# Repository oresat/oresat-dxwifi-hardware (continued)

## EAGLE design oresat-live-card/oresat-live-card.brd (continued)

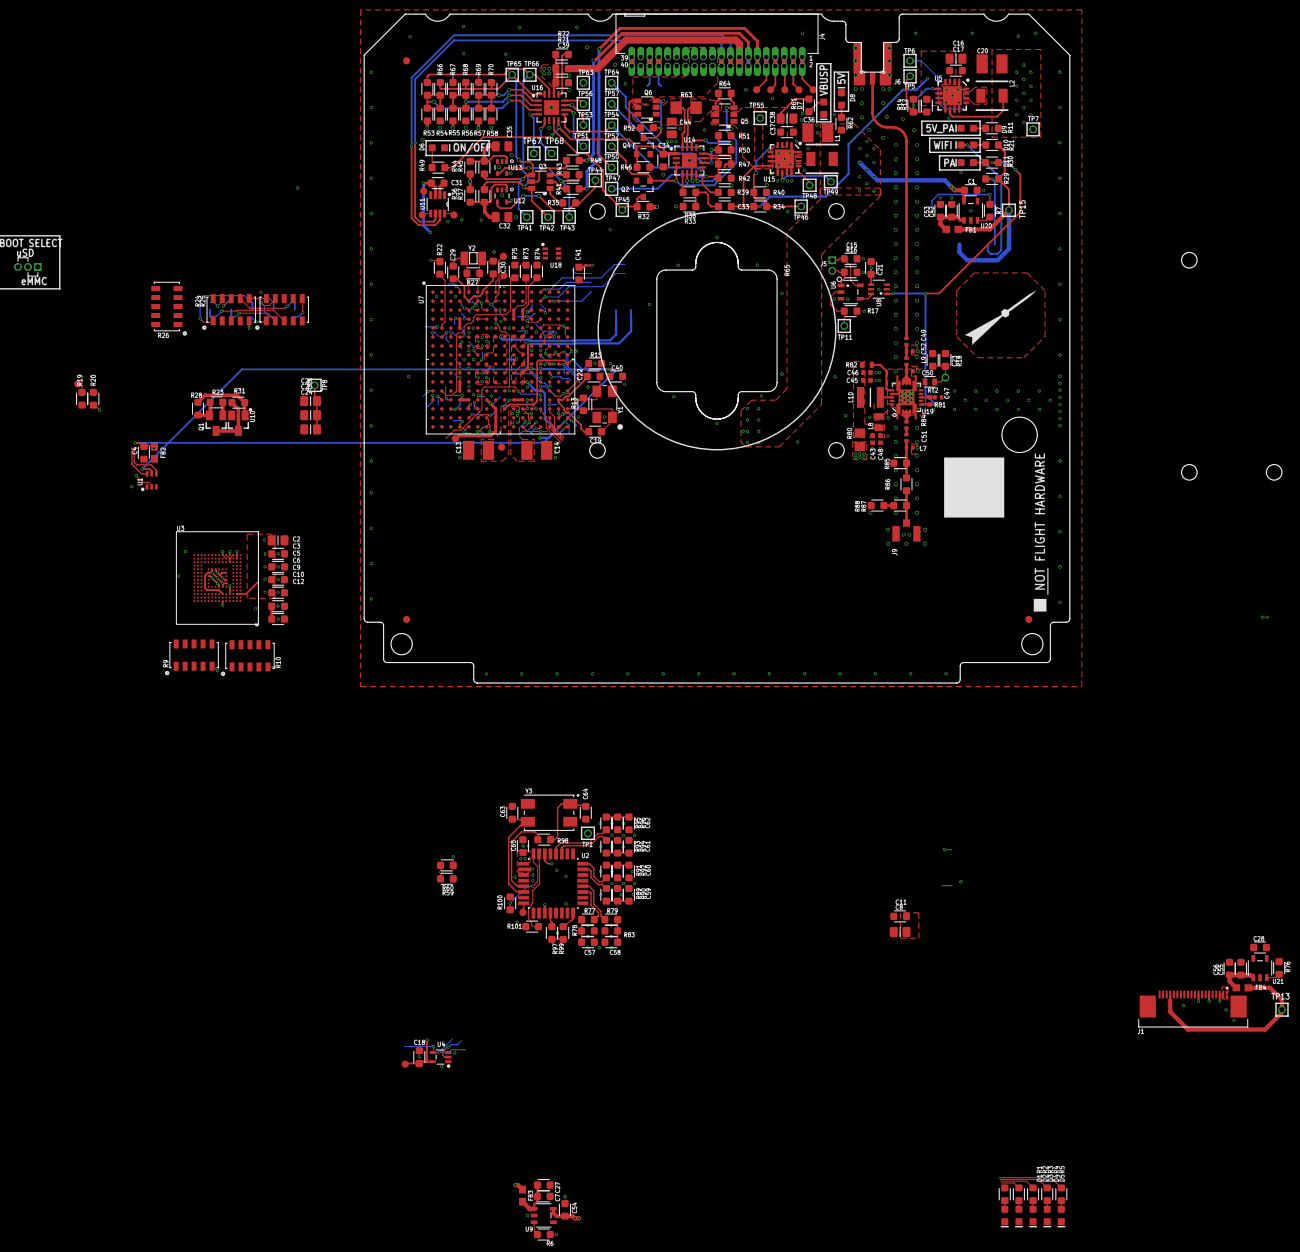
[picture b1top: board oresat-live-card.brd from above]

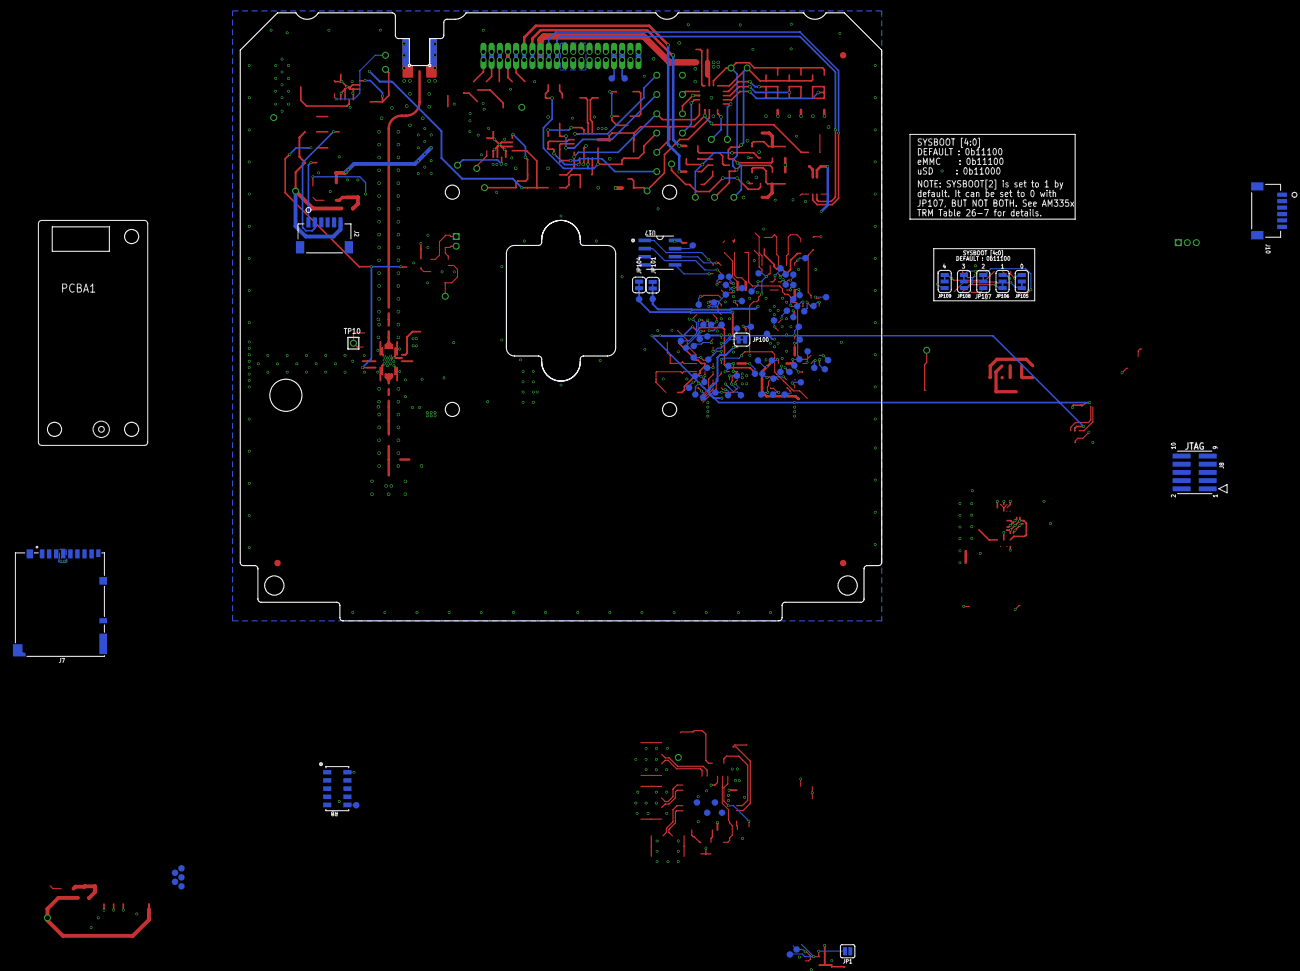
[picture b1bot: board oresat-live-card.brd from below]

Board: 4 copper layers, 99.8 x 94.6 mm, 376 parts (102 on the bottom side), 292 nets.

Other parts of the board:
U$2, U$5, U$6: FIDUCIAL_G10
U$3: PSAS_LOGO_10X10
U$4: FLIGHTMARKER_NEW_BOARDS

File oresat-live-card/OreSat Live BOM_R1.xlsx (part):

Part | Qty per board | Extended Qty | Extras | Qty Needed | Qty on Hand | Qty to Order | Value | Package | MFR | MPN | Alt MFR | Alt MPN | DESCRIPTION
C1, C2, C7, C8, C16, C38, C44 | 7 | 28 | 2 | 30 | 9 | 20 | 10uF | .0805-B | TDK Corporation | CGA4J1X7S1C106M125AE |  | CGA4J1X7S1C106K125AE | CAP CER 10UF 16V X7S 0805
C13, C14, C20, C36 | 4 | 16 | 4 | 20 | 15 | 5 | 22uF | C1210 | TDK Corporation | CGA6P1X7R1C226M250AC |  |  | CAP CER 22UF 16V X7R 1210
C19, C22, C29, C30 | 4 | 16 | 4 | 20 | 8 | 10 | 12pF | .0603-A | TDK Corporation | CGA3E2C0G1H120J080AA |  |  | CAP CER 12PF 50V C0G 0603
C24, C25 | 2 | 8 | 2 | 10 | 4 | 10 | 1000PF | .0805-B | TDK Corporation | CGA4F2X7R2A102K085AE |  |  | CAP CER 1000PF 100V X7R 0805
C26 | 1 | 4 | 6 | 10 | 7 | 0 | 0.1uF | .0805-B | TDK Corporation | CGA4J2X7R1H104K125AE |  |  | CAP CER 0.1UF 50V X7R 0805
C3, C5, C6, C9, C10, C12, C17, C33, C34, C37 | 10 | 40 | 10 | 50 | 20 | 30 | 1uF | .0603-A | TDK Corporation | CGA3E1X7R1C105K080AC |  |  | CAP CER 1UF 16V X7R 0603
C32, C35 | 2 | 8 | 2 | 10 | 4 | 10 | 1uF | .0805-B-NOSILK | TDK Corporation | CGA4J2X7R1C105K125AA |  |  | CAP CER 1UF 16V X7R 0805
C4, C11, C15, C18, C21, C23, C31, C39, C40, C41 | 10 | 40 | 10 | 50 | 17 | 30 | 0.1uF | .0603-A | TDK Corporation | CGA3E2X7R1E104K080AA |  |  | CAP CER 0.1UF 25V X7R 0603
C43, C45, C46, C47 | 4 | 16 | 4 | 20 | 8 | 10 | 0.1uF | .0402-B-NOSILK | TDK Corporation | CGA2B1X7R1C104K050BC |  |  | CAP CER 0.1UF 16V X7R 0402
C48 | 1 | 4 | 6 | 10 | 14 | 0 | 1000pF | .0402-B-NOSILK | TDK Corporation | CGA2B2NP01H102J050BA |  |  | CAP CER 1000PF 50V NP0 0402
C49 | 1 | 4 | 6 | 10 | 25 | 0 | 100pF | .0402-C-NOSILK | Murata | GCM1555C1H101GA16D |  |  | CAP CER 100PF 50V C0G/NP0 0402
C50 | 1 | 4 | 6 | 10 | 3 | 10 | 3.0pF | .0402-C-NOSILK | AVX | 04025U3R0BAT2A |  |  | CAP CER 3PF 50V NP0 0402
C51 | 1 | 4 | 6 | 10 | 1 | 10 | 1.1pF | .0402-C-NOSILK | AVX | 04025J1R1PBSTR\500 |  |  | 50V 1.1pF .02pFTol ThinFilm 0402
C51a | 1 | 4 | 6 | 10 | 1 | 10 | 1.4pF | .0402-C-NOSILK | AVX | 04025J1R4PBSTR\500 |  |  | 50V 1.4pF .02pFTol ThinFilm 0402
C52 | 1 | 4 | 6 | 10 | 3 | 10 | 1.6pF | .0402-C-NOSILK | AVX | 04025U1R6BAT2A |  |  | CAP CER 1.6PF 50V NP0 0402
D1, D7, D8 | 3 | 12 | 3 | 15 | 5 | 10 | GREEN | LED-0603 | Würth Elektronik | 150060GS75020 |  |  | Green 525nm LED 3.2V 0603
D2, D3, D4, D5 | 4 | 16 | 4 | 20 | 8 | 10 | BLUE | LED-0603 | Würth Elektronik | 150060BS75020 |  |  | Blue 470nm LED 3.2V 0603
D6 | 1 | 4 | 6 | 10 | 10 | 0 | GREEN | LED-0603 | Würth Elektronik | 150060VS55040 |  |  | Green 573nm LED 2V 0603
D9, D10 | 2 | 8 | 2 | 10 | 1 | 10 | GREEN | LED-0603 | Lite-On Inc. | LTST-C193KGKT-5A |  |  | Green 572nm LED 2V 0603
D11 | 1 | 4 | 6 | 10 | 8 | 0 | RED | LED-0603 | Lite-On Inc. | LTST-C193KRKT-5A |  |  | Red 631nm LED 2V 0603
FB1, FB2 | 2 | 8 | 2 | 10 | 4 | 10 | 30Ω/1.8A | 0603 | Murata Electronics | BLM18KG300JH1D |  |  | FERRITE BEAD 30 OHM 0603 1 LN
J1 | 1 | 4 | 1 | 5 | 3 | 2 | ORESAT-DEBUG-CONNECTOR-CARD | TE_2-1734592-0 | TE Connectivity AMP Connectors | 2-1734592-0 |  |  | CONN FPC BOTTOM 20POS 0.50MM R/A
J2 | 1 | 4 | 1 | 5 | 3 | 2 | SM06B-SRSS-TB(LF)(SN) | CONN_SM06B-SRSS-TB_JST | JST Sales America Inc. | SM06B-SRSS-TB(LF)(SN) |  |  | CONN HEADER SMD R/A 6POS 1MM
J4 | 1 | 4 | 1 | 5 | 0 | 5 | TFM-120-01-L-D-RA | J-SAMTEC-TFM-120-X1-XXX-D-RA | Samtec Inc. | TFM-120-01-L-D-RA |  |  | CONN HEADER R/A 40POS 1.27MM
J6 | 1 | 4 | 1 | 5 | 5 | 0 | J-MOLEX-SMPM-73300-003X | J-MOLEX-SMPM-073300-003X | MOLEX | 0733000020 |  |  | CONN SMPM PLUG STR EDGEMNT
J7 | 1 | 4 | 1 | 5 | 2 | 3 | DM3BT-DSF-PEJS | DM3BT-DSF-PEJS | Hirose Electric Co Ltd | DM3BT-DSF-PEJS |  |  | CONN MICRO SD CARD PUSH-PUSH R/A
J9 | 1 | 4 | 1 | 5 | 3 | 2 | U.FL-R-SMA | U.FL-R-SMT | Hirose Electric Co Ltd | U.FL-R-SMT-1(10) |  |  | CONN U.FL RCPT STR 50 OHM SMD
L1,L2 | 2 | 8 | 2 | 10 | 4 | 6 | 6.8uH | ECS-MPI4040 | ECS Inc. | ECS-MPI4040R4-6R8-R |  |  | FIXED IND 6.8UH 2.4A 91 MOHM SMD
L7 | 1 | 4 | 6 | 10 | 5 | 0 | 1.7nH | .0402-C-NOSILK | Coilcraft | 0402DC-1N7XJRU |  |  | 1.7nH RF Inductor, ceramic core, 5% tol
L8 | 1 | 4 | 6 | 10 | 4 | 0 | 6.8nH | .0805-C-NOSILK | Coilcraft | 0805CS-060XJLC |  |  | Fixed Inductors 0805CS 6.8 nH 5 % 0.6 A
L9 | 1 | 4 | 6 | 10 | 13 | 0 | 1.0nH | .0402-C-NOSILK | TDK Corporation | MLK1005S1N0ST000 |  |  | FIXED IND 1NH 500MA 100 MOHM SMD
L10 | 1 | 4 | 6 | 10 | 3 | 2 | 10nH | INDC2928X203N | Coilcraft | 1008HQ-10NXJLB |  |  | Fixed Inductors 1008 10nH Unshld 5%
Q1 | 1 | 4 | 2 | 6 | 3 | 2 | MMBT2907 | SOT23-BEC | Diodes Incorporated | MMBT2907A-7-F |  |  | TRANS PNP 60V 0.6A SOT23-3
Q2, Q4 | 2 | 8 | 2 | 10 | 4 | 6 | PMV45EN | SOT23 | Nexperia USA Inc. | PMV45EN2R |  |  | MOSFET N-CH 30V 4.1A TO236AB
Q3 | 1 | 4 | 2 | 6 | 3 | 2 | DMP2240UDM | SOT23-6 | Diodes Incorporated | DMP2240UDM-7 |  |  | MOSFET 2P-CH 20V 2A SOT-26
Q5, Q6 | 2 | 8 | 2 | 10 | 4 | 6 | MOSFET-PCH-SOT23-6 | SOT23-6 | Diodes Incorporated | DMP3050LVT-7 |  |  | MOSFET P CH 30V 4.5A TSOT26
R1, R2, R3, R4, R5, R21, R30 | 7 | 28 | 4 | 32 | 11 | 20 | 1k | .0603-A | Panasonic Electronic Components | ERJ-3EKF1001V |  | ERJ-U03F1001V | RES SMD 1K OHM 1% 1/10W 0603
R11, R49, R61, R62 | 4 | 16 | 4 | 20 | 8 | 10 | 2.7k | .0603-A | Panasonic Electronic Components | ERJ-3EKF2701V |  | ERJ-U03F2701V | RES SMD 2.7K OHM 1% 1/10W 0603
R13, R36, R44 | 3 | 12 | 3 | 15 | 6 | 10 | 1M | .0603-A | Panasonic Electronic Components | ERJ-3EKF1004V |  | ERJ-U03F1004V | RES SMD 1M OHM 1% 1/10W 0603
R23 | 1 | 4 | 6 | 10 | 6 | 10 | 499 | .0603-A | Panasonic Electronic Components | ERJ-3EKF4990V |  |  | RES SMD 499 OHM 1% 1/10W 0603
R24, R25, R26 | 3 | 12 | 3 | 15 | 6 | 10 | 100K | ARRAY_EXBA-M | Panasonic Electronic Components | EXB-A10P104J |  |  | RES ARRAY 8 RES 100K OHM 2512
R29, R47, R50 | 3 | 12 | 3 | 15 | 13 | 0 | 0 | .0603-A | Panasonic Electronic Components | ERJ-3GEY0R00V |  |  | RES SMD 0 OHM JUMPER 1/10W 0603
R31 | 1 | 4 | 6 | 10 | 7 | 10 | 40.2K | .0603-A | Panasonic Electronic Components | ERJ-3EKF4022V |  |  | RES SMD 40.2K OHM 1% 1/10W 0603
R33 | 1 | 4 | 6 | 10 | 7 | 10 | 100k | .0603-A | Panasonic Electronic Components | ERJ-PA3F1003V |  |  | RES SMD 100K OHM 1% 1/4W 0603
R35, R43 | 2 | 8 | 2 | 10 | 4 | 10 | 665k | .0603-A | Panasonic Electronic Components | ERJ-3EKF6653V |  |  | RES SMD 665K OHM 1% 1/10W 0603
R37, R45 | 2 | 8 | 2 | 10 | 4 | 10 | 330k | .0603-A | Panasonic Electronic Components | ERJ-3EKF3303V |  |  | RES SMD 330K OHM 1% 1/10W 0603
R41, R48, R71, R73, R74, R75 | 6 | 24 | 4 | 28 | 10 | 20 | 100 | .0603-A | Panasonic Electronic Components | ERJ-3EKF1000V |  |  | RES SMD 100 OHM 1% 1/10W 0603
R6, R7, R12, R15, R16, R17, R18, R19, R20, R22, R28, R32, R34, R38, R39, R46, R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 | 19 | 76 | 24 | 100 | 43 | 50 | 10k | .0603-A | Panasonic Electronic Components | ERJ-3EKF1002V |  | ERJ-U03F1002V | RES SMD 10K OHM 1% 1/10W 0603
R63 | 1 | 4 | 2 | 6 | 3 | 2 | 100m | R1206 | Vishay Dale | RCWE1206R100FKEA |  |  | RES 0.1 OHM 1% 1/2W 1206
R8, R9, R10 | 3 | 12 | 3 | 15 | 9 | 6 | 10K | ARRAY_EXBA-M | Panasonic Electronic Components | EXB-A10P103J |  |  | RES ARRAY 8 RES 10K OHM 2512
R80 | 1 | 4 | 6 | 10 | 14 | 0 | 0 | R0805 | Panasonic Electronic Components | ERJ-6GEY0R00V |  |  | RES SMD 0 OHM JUMPER 1/8W 0805
R81 | 1 | 4 | 6 | 10 | 13 | 0 | 110 | .0402-B-NOSILK | Panasonic Electronic Components | ERJ-2RKF1100X |  | ERJ-U02F1100X | RES SMD 110 OHM 1% 1/10W 0402
R82 | 1 | 4 | 6 | 10 | 14 | 0 | 220 | .0603-C-NOSILK | Panasonic Electronic Components | ERJ-3EKF2200V |  | ERJ-U03F2200V | RES SMD 220 OHM 1% 1/10W 0603
R84 | 1 | 4 | 6 | 10 | 17 | 0 | 3.3 | .0402-C-NOSILK | Vishay / Dale | CRCW04023R30FKED |  |  | RES SMD 3.3 OHM 1% 1/16W 0402
R85 | 1 | 4 | 6 | 10 | 7 | 0 | 82.5 | .0603-A | Panasonic Electronic Components | ERJ-3EKF82R5V |  |  | RES SMD 82.5 OHM 1% 1/10W 0603
R86 | 1 | 4 | 6 | 10 | 7 | 0 | 93.1 | .0603-A | Panasonic Electronic Components | ERJ-3EKF93R1V |  |  | RES SMD 93.1 OHM 1% 1/10W 0603
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
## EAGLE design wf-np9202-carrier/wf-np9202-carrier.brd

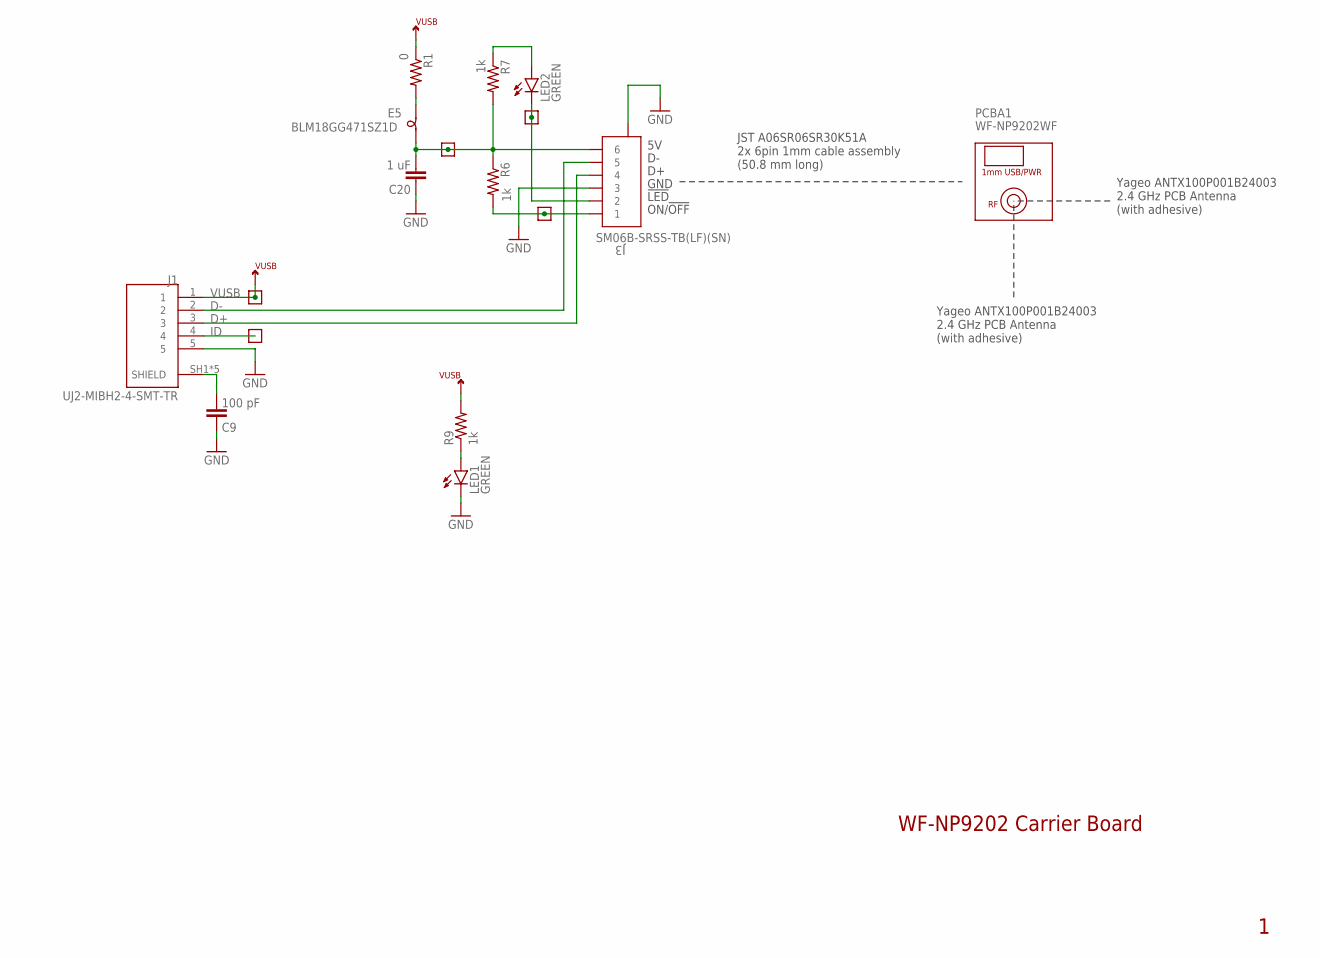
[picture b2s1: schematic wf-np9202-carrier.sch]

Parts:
C9: 100 pF; .0603-C-NOSILK
C20: 1 uF; .0603-B-NOSILK
E5: BLM18GG471SZ1D; .0603-B
ID: TEST-POINT-LARGE-SQUARE; 1X01
J1: UJ2-MIBH2-4-SMT-TR; CUI_UJ2-MIBH2-4-SMT-TR
J3: SM06B-SRSS-TB(LF)(SN); CONN_SM06B-SRSS-TB_JST
LED1, LED2: GREEN; LED-0603
PCBA1: WF-NP9202WF; WF-NP9202
R1: 0; .0603-B-NOSILK
R6, R7, R9: 1k; .0603-B-NOSILK
TP1, TP3, TP4, TP5: TEST-POINT-LARGE-SQUARE; 1X01

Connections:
D+: J1.3, J3.4
D-: J1.2, J3.5
GND: C9.1, C20.1, J1.5, J3.3, J3.7, J3.8 (7), LED1.C
ID: ID.1, J1.4
unnamed: C9.2, J1.SH1 (SHIELD), J1.SH2 (SHIELD), J1.SH3 (SHIELD), J1.SH4 (SHIELD), J1.SH5 (SHIELD)
unnamed: LED1.A, R9.1
unnamed: C20.2, E5.2, J3.6, R6.1, R7.2, TP3.1
unnamed: E5.1, R1.2
unnamed: J3.1, R6.2, TP4.1
unnamed: LED2.A, R7.1
unnamed: J3.2, LED2.C, TP5.1
VUSB: J1.1, R1.1, R9.2, TP1.1

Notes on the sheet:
WF-NP9202 Carrier Board
GND
!LED
ON/!OFF
JST A06SR06SR30K51A 2x 6pin 1mm cable assembly (50.8 mm long)
Yageo ANTX100P001B24003 2.4 GHz PCB Antenna (with adhesive)

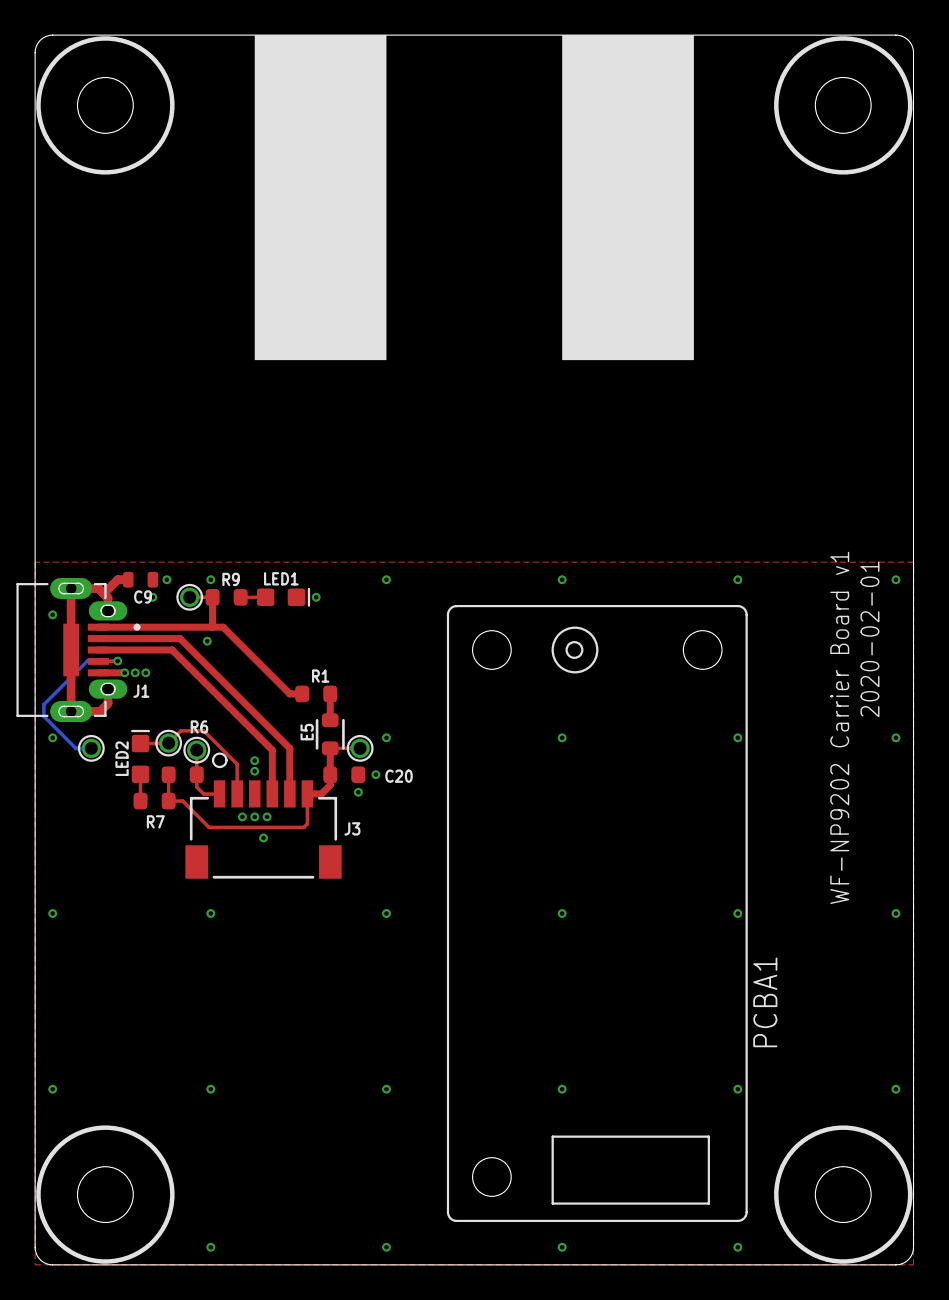
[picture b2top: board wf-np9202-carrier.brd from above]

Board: 2 copper layers, 50.0 x 70.0 mm, 21 parts (0 on the bottom side), 12 nets.

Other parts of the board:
U$1, U$2, U$3, U$4: #4/.300-BARE+STD_NUT_OR_STAR_WASHER

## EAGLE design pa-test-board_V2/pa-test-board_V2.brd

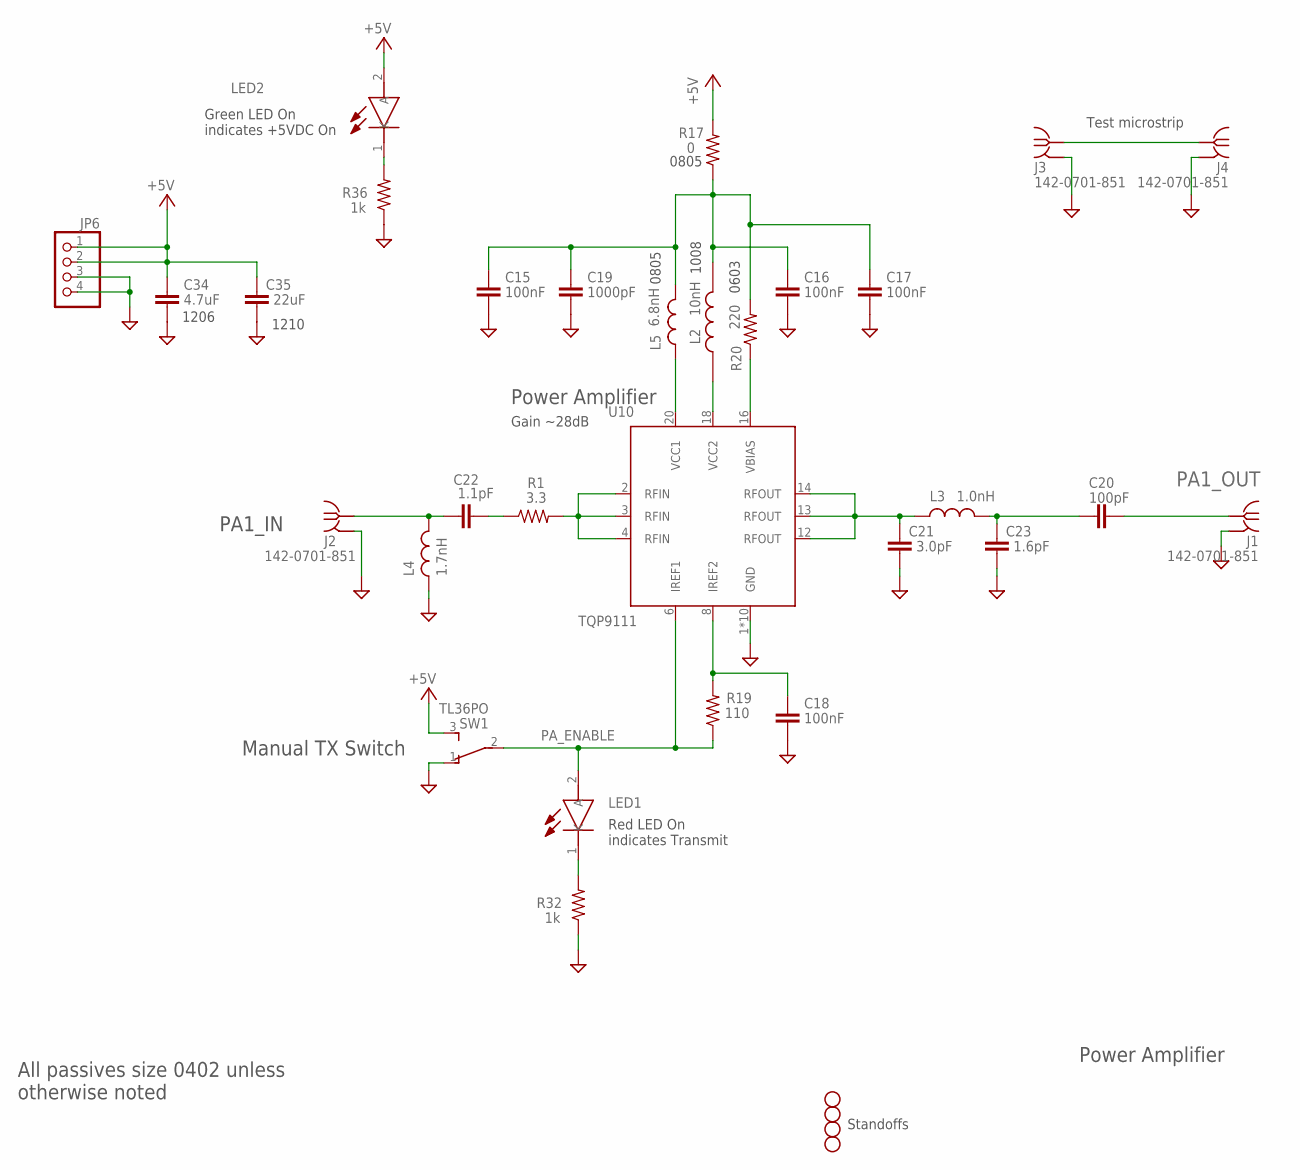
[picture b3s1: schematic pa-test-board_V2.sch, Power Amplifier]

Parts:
C15, C16, C17: 100nF; .0402-B-NOSILK; MPN CGA2B1X7R1C104K050BC
C18: 100nF; .0402-C-NOSILK; MPN CGA2B1X7R1C104K050BC
C19: 1000pF; .0402-B-NOSILK; MPN CGA2B2NP01H102J050BA
C20: 100pF; .0402-C-NOSILK; MPN GCM1885C1H101JA16D
C21: 3.0pF; .0402-C-NOSILK; MPN 04025U3R0BAT2A
C22: 1.1pF; .0402-C-NOSILK; MPN 04025J1R1PBSTR\500
C23: 1.6pF; .0402-C-NOSILK; MPN 04025U1R6BAT2A
C34: 4.7uF; C1206; MPN GCJ31CR71C475KA01L
C35: 22uF; C1210; MPN GCJ32ER71C226KE01L
H1, H2, H3, H4: STAND-OFFTIGHT; STAND-OFF-TIGHT
J1, J2, J3, J4: 142-0701-851; MPN 142-0701-851
JP6: PINHD-1X4; 1X04; MPN 0022232041
L2: 10nH; INDC2928X203N
L3: 1.0nH; .0402-C-NOSILK; MPN MLK1005S1N0ST000
L4: 1.7nH; .0402-C-NOSILK; MPN 0402DC-1N7XJRU
L5: 6.8nH; .0805-C-NOSILK; MPN 0805CS-060XJLC
LED1: LTST-C193KRKT-5A; LEDC1607X80N
LED2: LTST-C193KGKT-5A; LEDC1607X80N
R1: 3.3; .0402-C-NOSILK; MPN CRCW04023R30FKED
R17: 0; R0805; MPN ERJ-6GEY0R00V
R19: 110; .0402-B-NOSILK; MPN ERJ-2RKF1100X
R20: 220; .0603-C-NOSILK; MPN ERJ-3EKF2200V
R32, R36: 1k; .0402-B-NOSILK; MPN ERJ-2GEJ102X
SW1: TL36PO; TL3XPO; MPN TL36P005000
U10: TQP9111; QFN50P400X400X102-21N

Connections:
+5V: C34.1, C35.1, JP6.1, JP6.2, LED2.2 (A), R17.2, SW1.3 (S)
GND: C15.2, C16.2, C17.2, C18.2, C19.2, C21.2, C23.2, C34.2, C35.2, J1.GND1 (GND), J1.GND2 (GND), J1.GND3 (GND), J1.GND4 (GND), J2.GND1 (GND), J2.GND2 (GND), J2.GND3 (GND), J2.GND4 (GND), J3.GND1 (GND), J3.GND2 (GND), J3.GND3 (GND), J3.GND4 (GND), J4.GND1 (GND), J4.GND2 (GND), J4.GND3 (GND), J4.GND4 (GND), JP6.3, JP6.4, L4.1, R32.1, R36.1, SW1.1 (O), U10.1 (GND), U10.5 (GND), U10.7 (GND), U10.9 (GND), U10.10 (GND), U10.11 (GND), U10.15 (GND), U10.17 (GND), U10.19 (GND), U10.21 (GND)
unnamed: C22.1, J2.RF1 (RF), L4.2
unnamed: J3.RF1 (RF), J4.RF1 (RF)
unnamed: L2.1, U10.18 (VCC2)
unnamed: C22.2, R1.1
unnamed: LED1.1 (K), R32.2
unnamed: C15.1, C16.1, C17.1, C19.1, L2.2, L5.2, R17.1, R20.2
unnamed: C18.1, R19.2, U10.8 (IREF2)
unnamed: C21.1, L3.1, U10.12 (RFOUT), U10.13 (RFOUT), U10.14 (RFOUT)
unnamed: C20.1, C23.1, L3.2
unnamed: R20.1, U10.16 (VBIAS)
unnamed: L5.1, U10.20 (VCC1)
unnamed: LED2.1 (K), R36.2
unnamed: R1.2, U10.2 (RFIN), U10.3 (RFIN), U10.4 (RFIN)
PA1_OUT: C20.2, J1.RF1 (RF)
PA_ENABLE: LED1.2 (A), R19.1, SW1.2, U10.6 (IREF1)

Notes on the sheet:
0805
0603
Power Amplifier
Gain ~28dB
PA1_IN
All passives size 0402 unless otherwise noted
1206
1210
Manual TX Switch
Red LED On indicates Transmit
Green LED On indicates +5VDC On
Standoffs
Test microstrip
1008

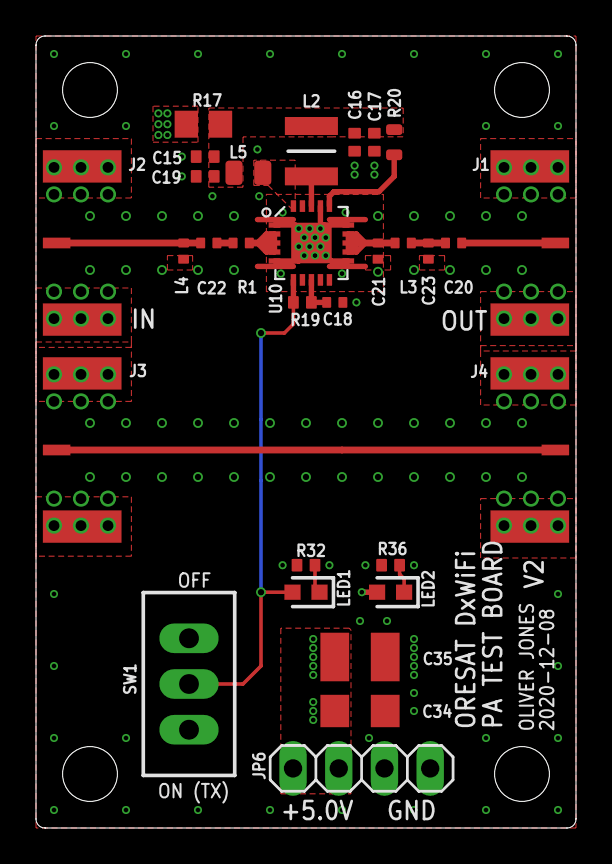
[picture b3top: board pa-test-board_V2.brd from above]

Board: 4 copper layers, 30.0 x 44.0 mm, 34 parts (0 on the bottom side), 17 nets.

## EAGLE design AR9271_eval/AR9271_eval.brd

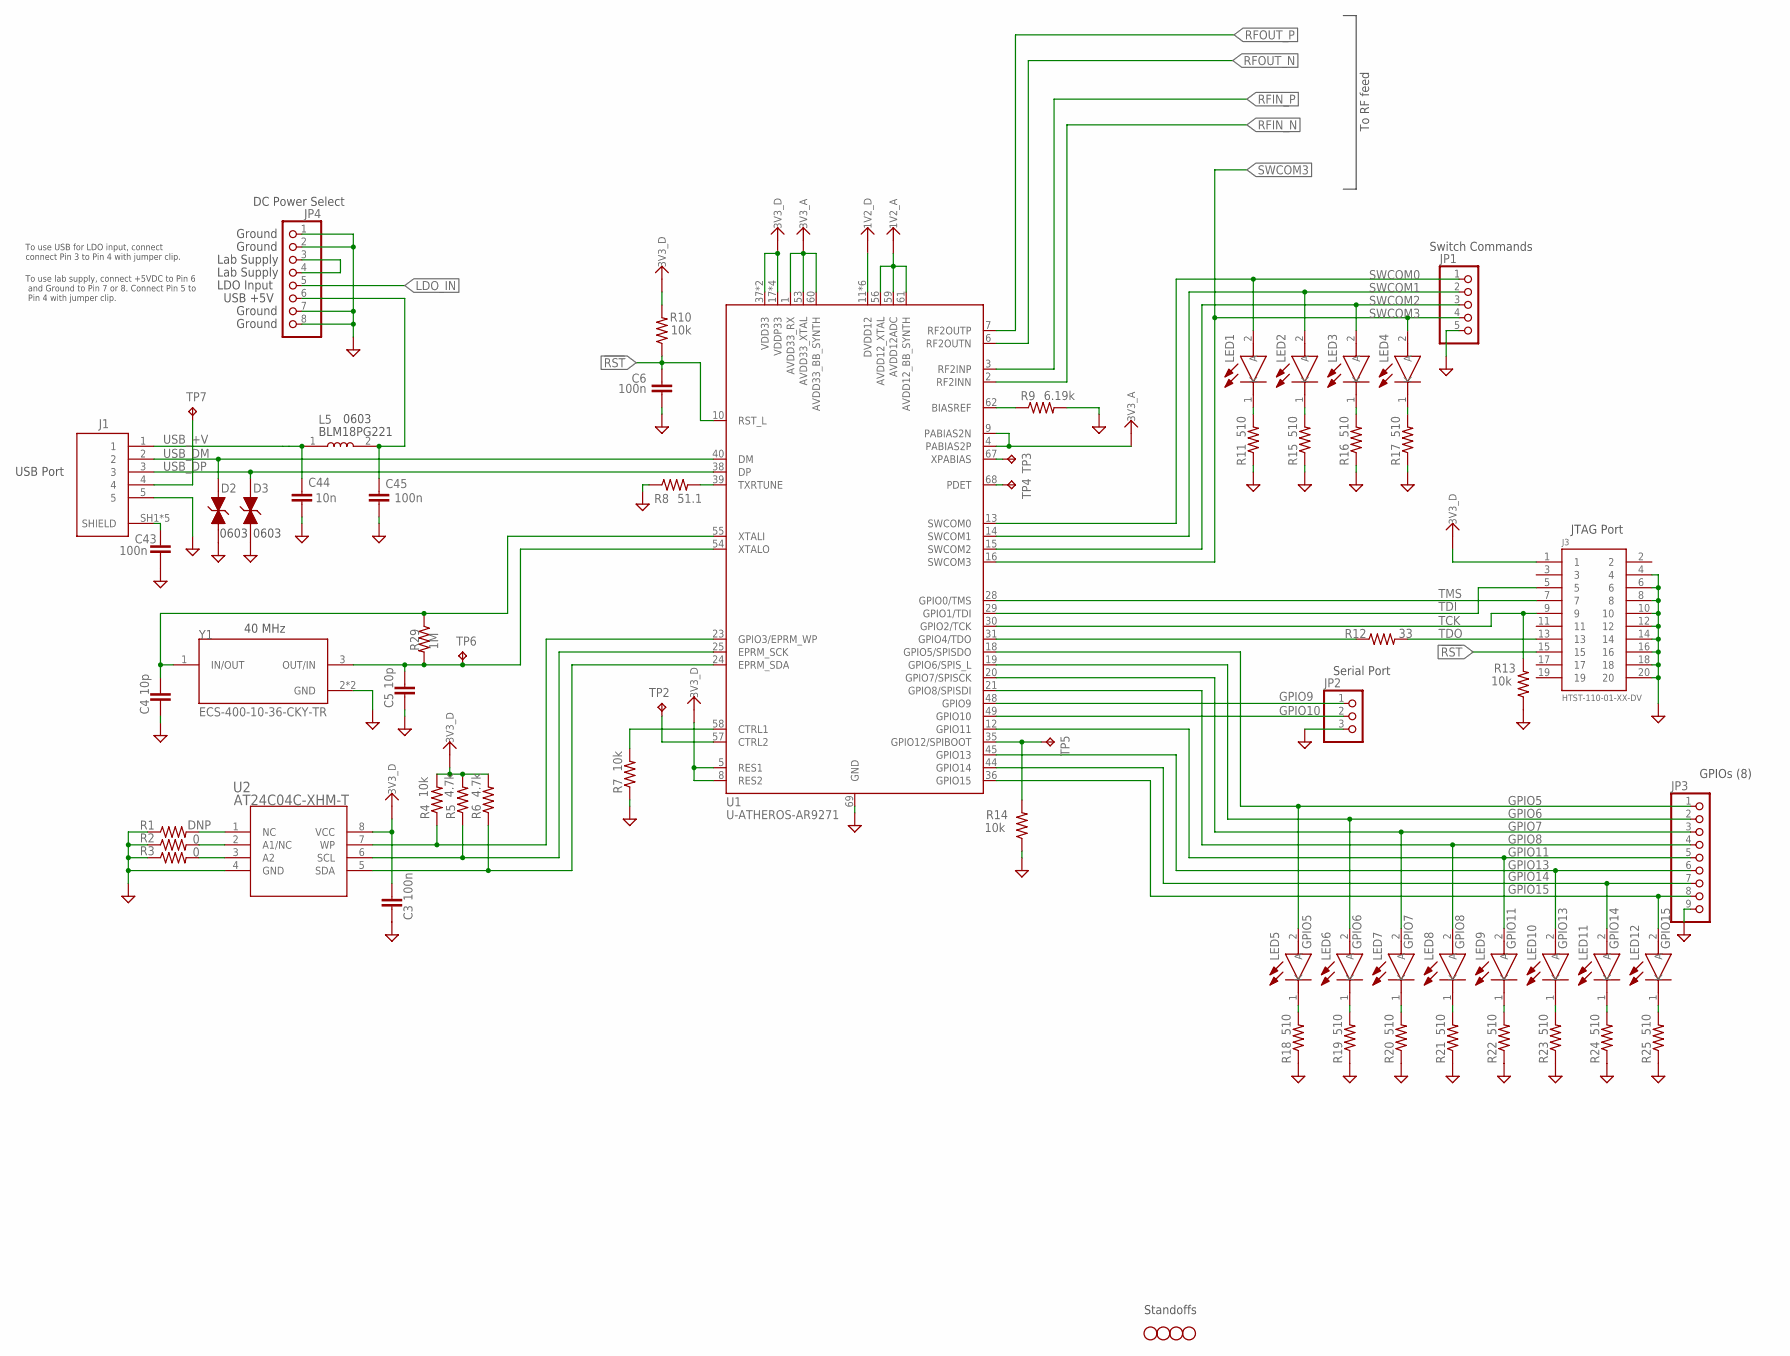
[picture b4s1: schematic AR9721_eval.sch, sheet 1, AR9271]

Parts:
C3, C6, C43, C45: 100n; .0402-B-NOSILK; MPN CGA2B1X7R1C104K050BC
C4, C5: 10p; .0402-B-NOSILK
C44: 10n; .0402-B-NOSILK; MPN C0402C103K4RACAUTO
D2, D3: PGB1010603MR; ESD_PGB1010603MR; MPN PGB1010603MR
H1, H2, H3, H4: STAND-OFFTIGHT; STAND-OFF-TIGHT
J1: UJ2-MIBH2-4-SMT-TR; CUI_UJ2-MIBH2-4-SMT-TR; MPN UJ2-MIBH2-4-SMT-TR
J3: HTST-110-01-XX-DV; MPN HTST-110-01-L-DV-P
JP1: PINHD-1X5; 1X05
JP2: PINHD-1X3; 1X03
JP3: PINHD-1X9; 1X09
JP4: PINHD-1X8; 1X08
L5: BLM18PG221SH1D; INDC1608X95; MPN BLM18PG221SH1D
LED1, LED2, LED3, LED4, LED5, LED6, LED7, LED8, LED9, LED10, LED11, LED12: LTST-C193KGKT-5A; LEDC1607X80N
R1: DNP; .0402-A-NOSILK; MPN ERJ-2GE0R00X
R2, R3: 0; .0402-A-NOSILK; MPN ERJ-2GE0R00X
R4, R7, R10, R13, R14: 10k; .0402-A-NOSILK; MPN ERJ-2GEJ103X
R5, R6: 4.7k; .0402-A-NOSILK; MPN ERJ-2GEJ103X
R8: 51.1; .0402-A-NOSILK; MPN ERJ-2RKF51R1X
R9: 6.19k; .0402-A-NOSILK; MPN ERJ-2RKF6191X
R11, R15, R16, R17, R18, R19, R20, R21, R22, R23, R24, R25: 510; .0402-A-NOSILK; MPN ERJ-2GEJ511X
R12: 33; .0402-A-NOSILK; MPN ERJ-2GEJ330X
R29: 1M; .0402-A-NOSILK; MPN ERJ-2GEJ105X
TP2, TP3, TP4, TP5, TP6, TP7: TPTP06R; TP06R
U1: U-ATHEROS-AR9271; QFN-68; MPN AR9271
U2: AT24C04C-XHM-T; 8X
Y1: ECS-400-10-36-CKY-TR; XTAL_ECS-400-10-36-CKY-TR

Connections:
1V2_A: U1.56 (AVDD12_XTAL), U1.59 (AVDD12ADC), U1.61 (AVDD12_BB_SYNTH); also elsewhere on the board
1V2_D: U1.11 (DVDD12), U1.22 (DVDD12), U1.27 (DVDD12), U1.42 (DVDD12), U1.43 (DVDD12), U1.46 (DVDD12); also elsewhere on the board
3V3_A: U1.1 (AVDD33_RX), U1.4 (PABIAS2P), U1.9 (PABIAS2N), U1.53 (AVDD33_XTAL), U1.60 (AVDD33_BB_SYNTH); also elsewhere on the board
3V3_D: C3.1, J3.1, R4.2, R5.2, R6.2, R10.2, U1.5 (RES1), U1.8 (RES2), U1.17 (VDDP33), U1.26 (VDDP33), U1.33 (VDDP33), U1.37 (VDD33), U1.41 (VDD33), U1.47 (VDDP33), U2.8 (VCC); also elsewhere on the board
!RST: C6.1, J3.15, R10.1, U1.10 (RST_L)
A1: R2.2, U2.2 (A1/NC)
A2: R3.2, U2.3 (A2)
BIASREF: R9.1, U1.62 (BIASREF)
CTRL1: R7.2, U1.58 (CTRL1)
CTRL2: TP2.TP, U1.57 (CTRL2)
EE-SCK: R5.1, U1.25 (EPRM_SCK), U2.6 (SCL)
EE-SDA: R6.1, U1.24 (EPRM_SDA), U2.5 (SDA)
EE-WP: R4.1, U1.23 (GPIO3/EPRM_WP), U2.7 (WP)
GND: C3.2, C4.2, C5.2, C6.2, C43.2, C44.2, C45.2, D2.2, D3.2, J1.5, J3.4, J3.6, J3.8, J3.10, J3.12, J3.14, J3.16, J3.18, J3.20, JP1.5, JP2.3, JP3.9, JP4.1, JP4.2, JP4.7, JP4.8, R1.1, R2.1, R3.1, R7.1, R8.1, R9.2, R11.1, R13.1, R14.1, R15.1, R16.1, R17.1, R18.1, R19.1, R20.1, R21.1, R22.1, R23.1, R24.1, R25.1, U1.69 (GND), U2.4 (GND), Y1.2 (GND), Y1.4 (GND); also elsewhere on the board
GPIO5: JP3.1, LED5.2 (A), U1.18 (GPIO5/SPISDO)
GPIO6: JP3.2, LED6.2 (A), U1.19 (GPIO6/SPIS_L)
GPIO7: JP3.3, LED7.2 (A), U1.20 (GPIO7/SPISCK)
GPIO8: JP3.4, LED8.2 (A), U1.21 (GPIO8/SPISDI)
GPIO9: JP2.1, U1.48 (GPIO9)
GPIO10: JP2.2, U1.49 (GPIO10)
GPIO11: JP3.5, LED9.2 (A), U1.12 (GPIO11)
GPIO13: JP3.6, LED10.2 (A), U1.45 (GPIO13)
GPIO14: JP3.7, LED11.2 (A), U1.44 (GPIO14)
GPIO15: JP3.8, LED12.2 (A), U1.36 (GPIO15)
LDO_IN: JP4.5; also elsewhere on the board
unnamed: J1.4, TP7.TP
unnamed: JP4.3, JP4.4
unnamed: R1.2, U2.1 (NC)
unnamed: LED1.1 (K), R11.2
unnamed: LED2.1 (K), R15.2
unnamed: LED3.1 (K), R16.2
unnamed: LED4.1 (K), R17.2
unnamed: LED5.1 (K), R18.2
unnamed: LED6.1 (K), R19.2
unnamed: LED7.1 (K), R20.2
unnamed: LED8.1 (K), R21.2
unnamed: LED9.1 (K), R22.2
unnamed: C43.1, J1.SH1 (SHIELD), J1.SH2 (SHIELD), J1.SH3 (SHIELD), J1.SH4 (SHIELD), J1.SH5 (SHIELD)
unnamed: LED10.1 (K), R23.2
unnamed: LED11.1 (K), R24.2
unnamed: LED12.1 (K), R25.2
PDET: TP4.TP, U1.68 (PDET)
RFIN_N: U1.2 (RF2INN); also elsewhere on the board
RFIN_P: U1.3 (RF2INP); also elsewhere on the board
RFOUT_N: U1.6 (RF2OUTN); also elsewhere on the board
RFOUT_P: U1.7 (RF2OUTP); also elsewhere on the board
SPIBOOT: R14.2, TP5.TP, U1.35 (GPIO12/SPIBOOT)
SWCOM0: JP1.1, LED1.2 (A), U1.13 (SWCOM0)
SWCOM1: JP1.2, LED2.2 (A), U1.14 (SWCOM1)
SWCOM2: JP1.3, LED3.2 (A), U1.15 (SWCOM2)
SWCOM3: JP1.4, LED4.2 (A), U1.16 (SWCOM3); also elsewhere on the board
TCK: J3.9, R13.2, U1.30 (GPIO2/TCK)
TDI: J3.5, U1.29 (GPIO1/TDI)
TDO: J3.13, R12.2
TDO-PRE-RES: R12.1, U1.31 (GPIO4/TDO)
TMS: J3.7, U1.28 (GPIO0/TMS)
TXRTUNE: R8.2, U1.39 (TXRTUNE)
USB+5V: C45.1, JP4.6, L5.2
USB_+V: C44.1, J1.1, L5.1
USB_DM: D2.1, J1.2, U1.40 (DM)
USB_DP: D3.1, J1.3, U1.38 (DP)
XPABIOS: TP3.TP, U1.67 (XPABIAS)
XTALI: C4.1, R29.1, U1.55 (XTALI), Y1.1 (IN/OUT)
XTALO: C5.1, R29.2, TP6.TP, U1.54 (XTALO), Y1.3 (OUT/IN)

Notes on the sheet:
Lab Supply
LDO Input
USB +5V
Ground
To use USB for LDO input, connect connect Pin 3 to Pin 4 with jumper clip.
To use lab supply, connect +5VDC to Pin 6 and Ground to Pin 7 or 8. Connect Pin 5 to Pin 4 with jumper clip.
Serial Port
GPIOs (8)
JTAG Port
Switch Commands
USB Port
DC Power Select
BLM18PG221
0603
40 MHz
To RF feed
Standoffs

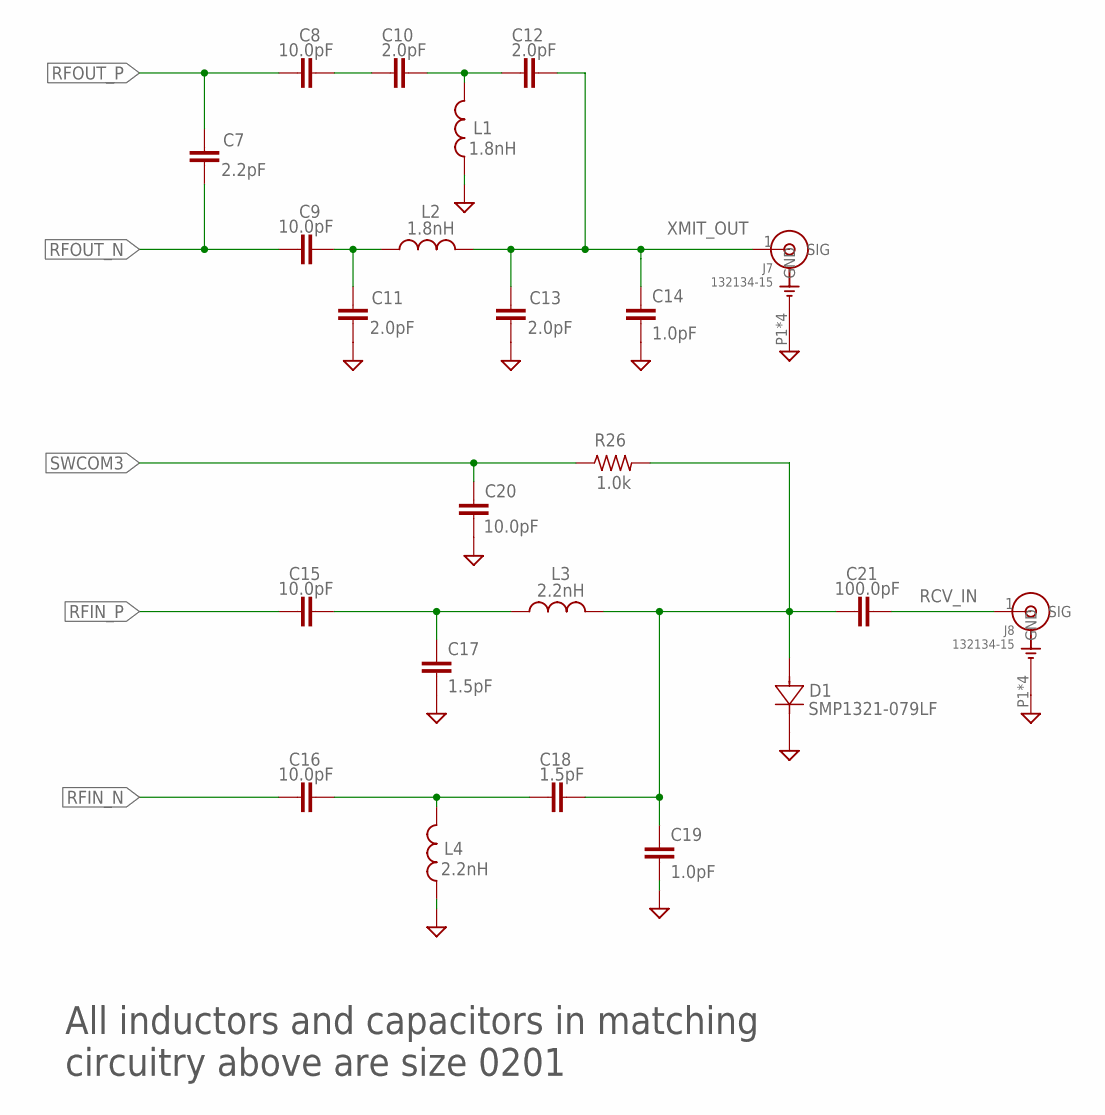
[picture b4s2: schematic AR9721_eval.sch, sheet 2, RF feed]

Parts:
C7: 2.2pF; .0201-B-NOSILK; MPN UMK063CG2R2CTHF
C8, C9, C15, C16, C20: 10.0pF; .0201-B-NOSILK; MPN UMK063CG100DTHF
C10, C11, C12, C13: 2.0pF; .0201-B-NOSILK; MPN UMK063CG020CTHF
C14, C19: 1.0pF; .0201-B-NOSILK; MPN UMK063CG010CTHF
C17, C18: 1.5pF; .0201-B-NOSILK; MPN UMK063CG1R5CT-F
C21: 100.0pF; .0201-B-NOSILK; MPN UMK063CG101JT-F
D1: SMP1321-079LF; SOD523
J7, J8: 132134-15; AMPHENOL_132134-15; MPN 132134-15
L1, L2: 1.8nH; .0201-B-NOSILK; MPN LQP03TN1N8B02D
L3, L4: 2.2nH; .0201-B-NOSILK; MPN LQP03TN2N2B02D
R26: 1.0k; .0201-B-NOSILK; MPN ERJ-1GNF1001C

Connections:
GND: C11.1, C13.1, C14.2, C17.2, C19.2, C20.2, D1.1, J7.P1 (GND), J7.P2 (GND), J7.P3 (GND), J7.P4 (GND), J8.P1 (GND), J8.P2 (GND), J8.P3 (GND), J8.P4 (GND), L1.1, L4.1; also elsewhere on the board
unnamed: C10.2, C12.1, L1.2
unnamed: C15.2, C17.1, L3.1
unnamed: C16.2, C18.1, L4.2
unnamed: C9.2, C11.2, L2.1
unnamed: C8.2, C10.1
unnamed: C18.2, C19.1, C21.1, D1.2, L3.2, R26.2
RCV_IN: C21.2, J8.1 (SIG)
RFIN_N: C16.1; also elsewhere on the board
RFIN_P: C15.1; also elsewhere on the board
RFOUT_N: C7.1, C9.1; also elsewhere on the board
RFOUT_P: C7.2, C8.1; also elsewhere on the board
SWCOM3: C20.1, R26.1; also elsewhere on the board
XMIT_OUT: C12.2, C13.2, C14.1, J7.1 (SIG), L2.2

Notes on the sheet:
All inductors and capacitors in matching circuitry above are size 0201
